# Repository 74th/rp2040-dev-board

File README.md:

# 74th が RP2040/RP2350 を手ではんだ付けしてみたくて作った開発ボード

- [Raspberry PI PICO と同じピン配置で、Flush のサイズを変えたいために、作った開発ボード rp2040 large board](./rp2040-large/)
- [ProMicro ピンアウト開発ボード rp2040 pro micro](./rp2040-promicro/)
- [RP2350の全てのピンを引き足した開発ボード（位置決め治具対応） RP2350A-Full](./rp2350a-full/)
- [RP2040の手はんだ実装支援用位置決め治具 RP2040 Solder Supporter](./rp2040-supporter/)
- [完成後のチェック用に使うファームウェア](rp2040-io-tester/) [rp2040-io-tester.uf2](rp2040-io-tester/rp2040-io-tester.uf2)
- [部品の調達先](./parts/)

## RP2040 手はんだ実装挑戦指南ガイド

74th の実装ノウハウをまとめたガイドを用意しています。初めて挑戦される方はぜひおよみください。

https://docs.google.com/document/d/1oHzV6qEClttqfrnbo-PlUElAemhTQe8-u3ijAKLZYF0/edit#heading=h.1b8zdysibsw9

## 使用しているシンボル、フットプリントライブラリ

https://github.com/74th/my-kicad-parts

## LICENSE

MIT

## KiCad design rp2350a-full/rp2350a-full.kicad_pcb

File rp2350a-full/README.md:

# RP2350A 手はんだ実装挑戦ボード

## v1.0.1

- 回路図 [PDF](./rp2350a-full_v1.0.1_semantics.pdf) [kicanvas](https://kicanvas.org/?github=https%3A%2F%2Fgithub.com%2F74th%2Frp2040-dev-board%2Fblob%2Frp2350-full%2F1.0.1%2Frp2350a-full%2Frp2350a-full.kicad_sch)
- PCB [kicanvas](https://kicanvas.org/?github=https%3A%2F%2Fgithub.com%2F74th%2Frp2040-dev-board%2Fblob%2Frp2350-full%2F1.0.1%2Frp2350a-full%2Frp2350a-full.kicad_pcb)

### Pin Map

### BOM

| Reference    | Name                              | Package         | Quantity |
| ------------ | --------------------------------- | --------------- | -------- |
| C1,C9-17,C19 | Capacitor 0.1uF                   | SMD I0603 M1608 | 11       |
| C2-4,C18     | Capacitor 4.7uF                   | SMD I0603 M1608 | 4        |
| C5-6         | Capacitor 7-33pF                    | SMD I0603 M1608 | 2        |
| C7-8         | Capacitor 10uF                    | SMD I0603 M1608 | 2        |
| D1           | LED Blue                          | SMD I0805 M2012 | 1        |
| J1           | USB Type-C Receptacle             |                 | 1        |
| J2           | Box Pin Header 2x5 Pitch 1.27mm   | TH              | 1        |
| L1           | Inductor 3.3uH                    | SMD I0806 M2016 | 1        |
| R1           | Resistor 200Ω                     | SMD I0603 M1608 | 1        |
| R2           | Resistor 1Ω                       | SMD I0603 M1608 | 1        |
| R3-4         | Resistor 27Ω                      | SMD I0603 M1608 | 2        |
| R5           | Resistor 33Ω                      | SMD I0603 M1608 | 1        |
| R6,R10       | Resistor 1kΩ                      | SMD I0603 M1608 | 2        |
| R7-8         | Resistor 5.1kΩ                    | SMD I0603 M1608 | 2        |
| R9,R11       | Resistor 10kΩ                     | SMD I0603 M1608 | 2        |
| SW1-2        | Button SKRPABE010                 |                 | 2        |
| U1           | MCU Raspberry Pi RP2350A          | QFN56           | 1        |
| U2           | USB Power Protection IC CH213K    | SOT-23          | 1        |
| U3           | Regulator 3.3V SOT-89 AMS1117-3.3 | SOT-90          | 1        |
| U4           | Flash W25Q32JVUU                  | USON-8          | 1        |
| Y1           | Crystal 12MHz                     | SMD 3225        | 1        |

## 実装の手順

実装したときの記録を記事にしています。こちらを実装前に参考にお読みいただけると良いかと思います。

https://74th.hateblo.jp/entry/2025/01/12/222618

かならずフラックスを用意してください。ブリッジした場合にはフラックスを塗って、はんだごてをあてて余分なフラックスを取り除きましょう。

以下の順序で実装することを推奨しています。

1. RP2350A(U1): RP2040 用の[位置決めボード](https://74th.booth.pm/items/5573498)を使えるなら使いましょう。手はんだ実装時のノウハウは
   https://docs.google.com/document/d/1oHzV6qEClttqfrnbo-PlUElAemhTQe8-u3ijAKLZYF0/edit#heading=h.1b8zdysibsw9 にまとめています。
2. USB Type-C: 受動部品実装前の方が、ランドを用いた疎通チェックがやりやすいため。[実装チェックツール](https://74th.booth.pm/items/5812941)を使うと便利です。
3. DCDC 用インダクタ(L1): 付近に囲むように他の部品があるため、先に実装します。
4. W25Q32VSS(U4): 裏面パッドに流すためのランドがあり、その付近に受動部品があり、後から実装が難しいため。
   - 裏面パッドのランドは他の部分より熱が伝わりにくいです。はんだが吸い込まれるまで、十分に加熱してください。
5. AMS1117-3.3(U3): 近くに CH213 があり、実装しにくいため。
6. CH213(U2)
7. 他の抵抗(R1-11)、キャパシタ(C1-19)、水晶発振器(Y1)、LED(D1)
8. スイッチ(SW1-2): サイズが大きく他の部品の実装の邪魔になるため、後から実装する

確認して実装ミスがなさそうであれば、電気的なチェックに進みましょう。

1. VBUS(VB)、5V、3V3、GND(G)間それぞれの抵抗値を計測し、短絡している（0Ω）となっている事がないことを確認する
2. USB を接続し、5V、3V3 と GND 間の電圧を測り、それぞれの電圧が正常であることを確認する
3. L1 と GND 間の電圧を測り、1.1V が出ていることを確認する。
4. PC に USB が認識されるか確認する。

全てのピンが実装できている稼働を確認するファームウェアを作っています。

各ピンが実装漏れている、若しくはブリッジしているのを確認するファームウェアを作っています。

https://github.com/74th/mcu-pin-check-firmware/

以下がファームウェアへのダイレクトリンクです。

https://github.com/74th/mcu-pin-check-firmware/raw/refs/heads/main/release/rp2350.uf2

GNDとジャンパをつなぎ、開発ボードの各スルーホールにジャンパのもう片方でタッチします。すると、USB CDCにてGPIO 8: L、GPIO 8: Hと出力されます。
これにて、全てのピンが接続され、ブリッジされていないことを確認してください。

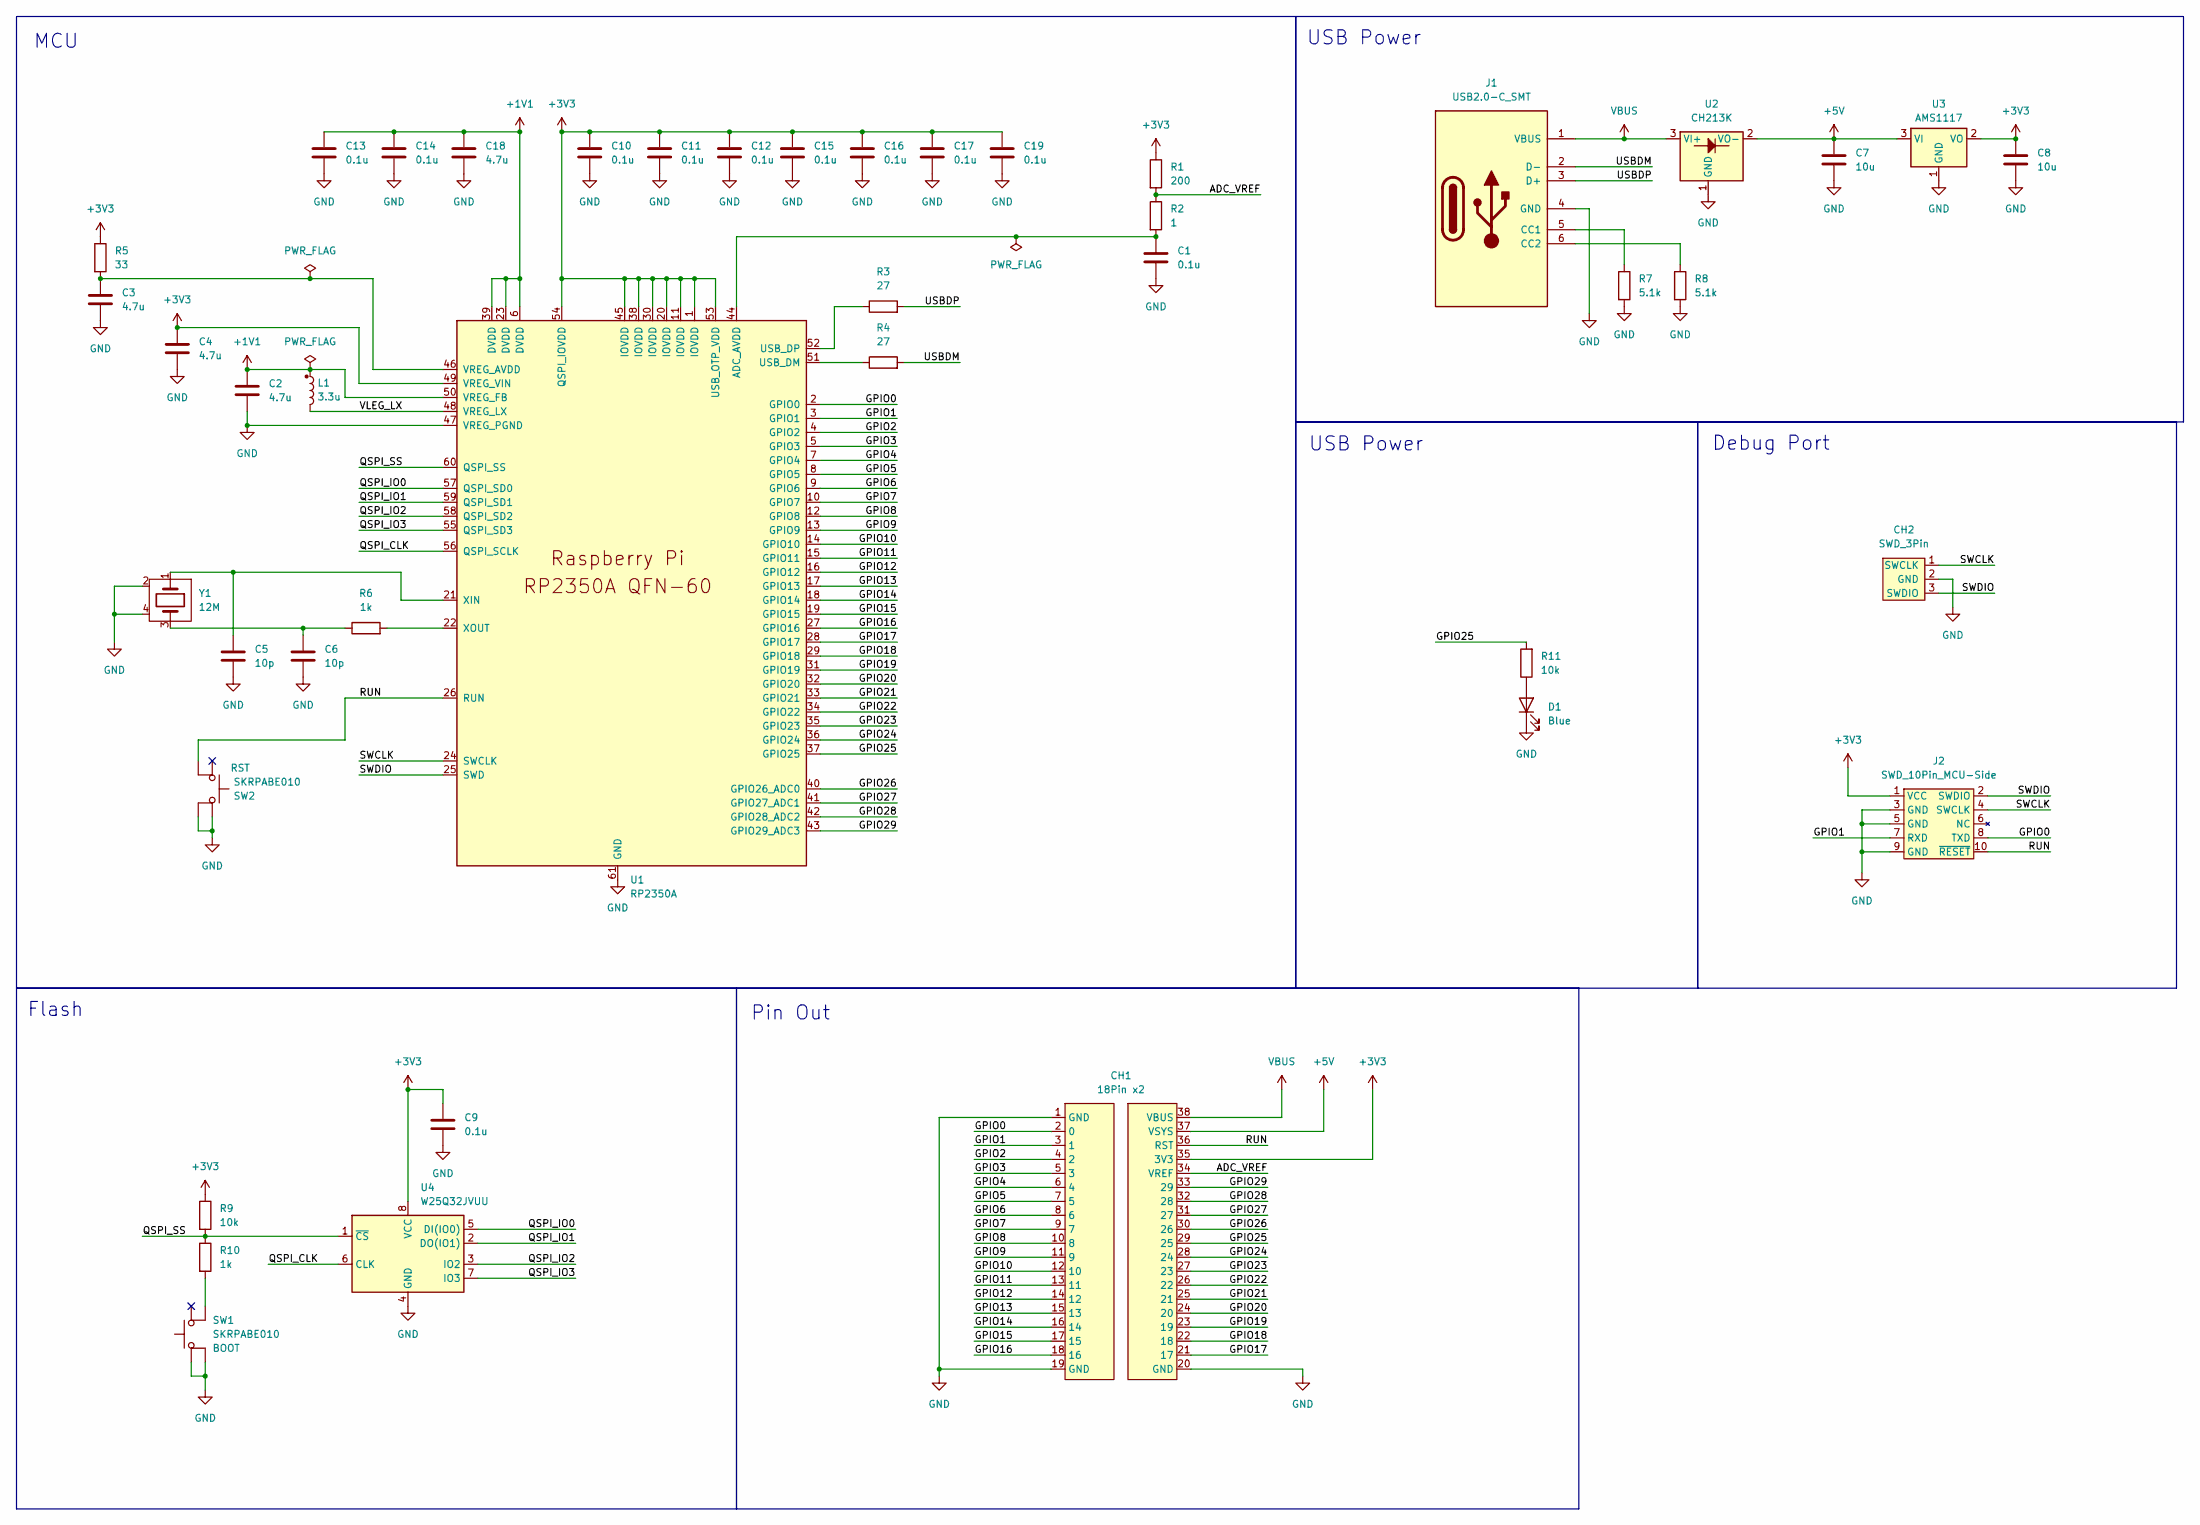
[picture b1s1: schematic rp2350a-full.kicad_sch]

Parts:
C1, C9, C10, C11, C12, C13, C14, C15, C16, C17, C19: 0.1u; Capacitor_0603_1608
C2, C3, C4, C18: 4.7u; Capacitor_0603_1608
C5, C6: 10p; Capacitor_0603_1608
C7, C8: 10u; Capacitor_0603_1608
CH1: 18Pin x2; PinOut_RP2350-Full
CH2: SWD_3Pin; PinOut_Pin_3_2GND
D1: Blue; LED_0805_2012
J1: USB2.0-C_SMT; Connector_USB-C-Receptacle_SMT_12-Pin_Simple
J2: SWD_10Pin_MCU-Side; Connector_HalfPinHeader_SWD
L1: 3.3u; Inductor_0806_2016
R1: 200; Register_0603_1608
R2: 1; Register_0603_1608
R3, R4: 27; Register_0603_1608
R5: 33; Register_0603_1608
R6, R10: 1k; Register_0603_1608
R7, R8: 5.1k; Register_0603_1608
R9, R11: 10k; Register_0603_1608
SW1, SW2: SKRPABE010; Switch_SKRPABE010_Pin-4
U1: RP2350A; Package_QFN-60-1EP_7x7mm_P0.4mm_EP3.4x3.4mm_hand
U2: CH213K; Package_SOT-23
U3: AMS1117; Package_SOT-89-3
U4: W25Q32JVUU; Package_USON-8_3x4mm_P0.8
Y1: 12M; Crystal_SMD_3225-4Pin_3.2x2.5mm_HandSoldering

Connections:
+1V1: C2.1, C13.1, C14.1, C18.1, L1.1, U1.6 (DVDD), U1.23 (DVDD), U1.39 (DVDD), U1.50 (VREG_FB)
+3V3: C4.1, C8.1, C9.1, C10.1, C11.1, C12.1, C15.1, C16.1, C17.1, C19.1, CH1.35 (3V3), J2.1 (VCC), R1.1, R5.1, R9.1, U1.1 (IOVDD), U1.11 (IOVDD), U1.20 (IOVDD), U1.30 (IOVDD), U1.38 (IOVDD), U1.45 (IOVDD), U1.49 (VREG_VIN), U1.53 (USB_OTP_VDD), U1.54 (QSPI_IOVDD), U3.2 (VO), U4.8 (VCC)
+5V: C7.1, CH1.37 (VSYS), U2.2 (VO-), U3.3 (VI)
/ADC_VREF: CH1.34 (VREF), R1.2, R2.1
/GPIO0: CH1.2 (0), J2.8 (TXD), U1.2 (GPIO0)
/GPIO1: CH1.3 (1), J2.7 (RXD), U1.3 (GPIO1)
/GPIO2: CH1.4 (2), U1.4 (GPIO2)
/GPIO3: CH1.5 (3), U1.5 (GPIO3)
/GPIO4: CH1.6 (4), U1.7 (GPIO4)
/GPIO5: CH1.7 (5), U1.8 (GPIO5)
/GPIO6: CH1.8 (6), U1.9 (GPIO6)
/GPIO7: CH1.9 (7), U1.10 (GPIO7)
/GPIO8: CH1.10 (8), U1.12 (GPIO8)
/GPIO9: CH1.11 (9), U1.13 (GPIO9)
/GPIO10: CH1.12 (10), U1.14 (GPIO10)
/GPIO11: CH1.13 (11), U1.15 (GPIO11)
/GPIO12: CH1.14 (12), U1.16 (GPIO12)
/GPIO13: CH1.15 (13), U1.17 (GPIO13)
/GPIO14: CH1.16 (14), U1.18 (GPIO14)
/GPIO15: CH1.17 (15), U1.19 (GPIO15)
/GPIO16: CH1.18 (16), U1.27 (GPIO16)
/GPIO17: CH1.21 (17), U1.28 (GPIO17)
/GPIO18: CH1.22 (18), U1.29 (GPIO18)
/GPIO19: CH1.23 (19), U1.31 (GPIO19)
/GPIO20: CH1.24 (20), U1.32 (GPIO20)
/GPIO21: CH1.25 (21), U1.33 (GPIO21)
/GPIO22: CH1.26 (22), U1.34 (GPIO22)
/GPIO23: CH1.27 (23), U1.35 (GPIO23)
/GPIO24: CH1.28 (24), U1.36 (GPIO24)
/GPIO25: CH1.29 (25), R11.2, U1.37 (GPIO25)
/GPIO26: CH1.30 (26), U1.40 (GPIO26_ADC0)
/GPIO27: CH1.31 (27), U1.41 (GPIO27_ADC1)
/GPIO28: CH1.32 (28), U1.42 (GPIO28_ADC2)
/GPIO29: CH1.33 (29), U1.43 (GPIO29_ADC3)
/QSPI_CLK: U1.56 (QSPI_SCLK), U4.6 (CLK)
/QSPI_IO0: U1.57 (QSPI_SD0), U4.5 (DI(IO0))
/QSPI_IO1: U1.59 (QSPI_SD1), U4.2 (DO(IO1))
/QSPI_IO2: U1.58 (QSPI_SD2), U4.3 (IO2)
/QSPI_IO3: U1.55 (QSPI_SD3), U4.7 (IO3)
/QSPI_SS: R9.2, R10.1, U1.60 (QSPI_SS), U4.1 (~CS)
/RUN: CH1.36 (RST), J2.10 (~RESET), SW2.4, U1.26 (RUN)
/SWCLK: CH2.1 (SWCLK), J2.4 (SWCLK), U1.24 (SWCLK)
/SWDIO: CH2.3 (SWDIO), J2.2 (SWDIO), U1.25 (SWD)
/USBDM: J1.2 (D-), R4.2
/USBDP: J1.3 (D+), R3.2
/VLEG_LX: L1.2, U1.48 (VREG_LX)
GND: C1.2, C2.2, C3.2, C4.2, C5.2, C6.2, C7.2, C8.2, C9.2, C10.2, C11.2, C12.2, C13.2, C14.2, C15.2, C16.2, C17.2, C18.2, C19.2, CH1.1 (GND), CH1.19 (GND), CH1.20 (GND), CH2.2 (GND), D1.1 (K), J1.4 (GND), J2.3 (GND), J2.5 (GND), J2.9 (GND), R7.2, R8.2, SW1.1, SW1.3, SW2.1, SW2.3, U1.47 (VREG_PGND), U1.61 (GND), U2.1 (GND), U3.1 (GND), U4.4 (GND), Y1.2, Y1.4
unnamed: C6.1, R6.1, Y1.3
unnamed: D1.2 (A), R11.1
unnamed: J1.5 (CC1), R7.1
unnamed: J1.6 (CC2), R8.1
unnamed: R10.2, SW1.4
unnamed: C1.1, R2.2, U1.44 (ADC_AVDD)
unnamed: R4.1, U1.51 (USB_DM)
unnamed: R3.1, U1.52 (USB_DP)
unnamed: C3.1, R5.2, U1.46 (VREG_AVDD)
unnamed: C5.1, U1.21 (XIN), Y1.1
unnamed: R6.2, U1.22 (XOUT)
VBUS: CH1.38 (VBUS), J1.1 (VBUS), U2.3 (VI+)

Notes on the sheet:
Flash
Pin Out
USB Power
Debug Port
MCU

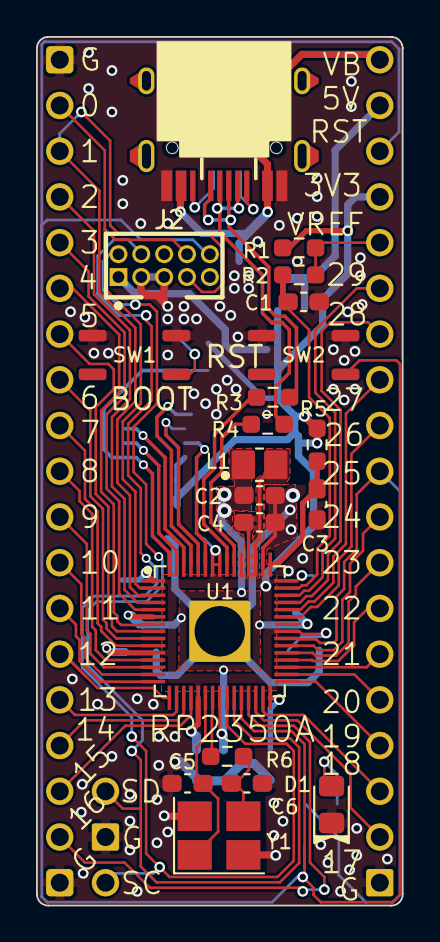
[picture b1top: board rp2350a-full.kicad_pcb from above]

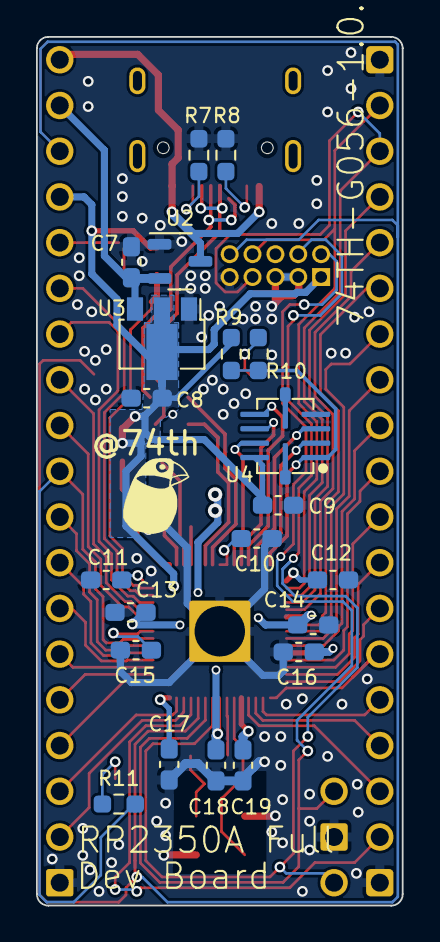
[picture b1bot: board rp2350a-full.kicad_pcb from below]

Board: 2 copper layers, 20.3 x 48.3 mm, 45 parts (23 on the bottom side), 59 nets.

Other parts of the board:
MISC-ACCOUNTTEXT: Logo_74th_text
MISC-ICON: LOGO; Logo_74th_5mm

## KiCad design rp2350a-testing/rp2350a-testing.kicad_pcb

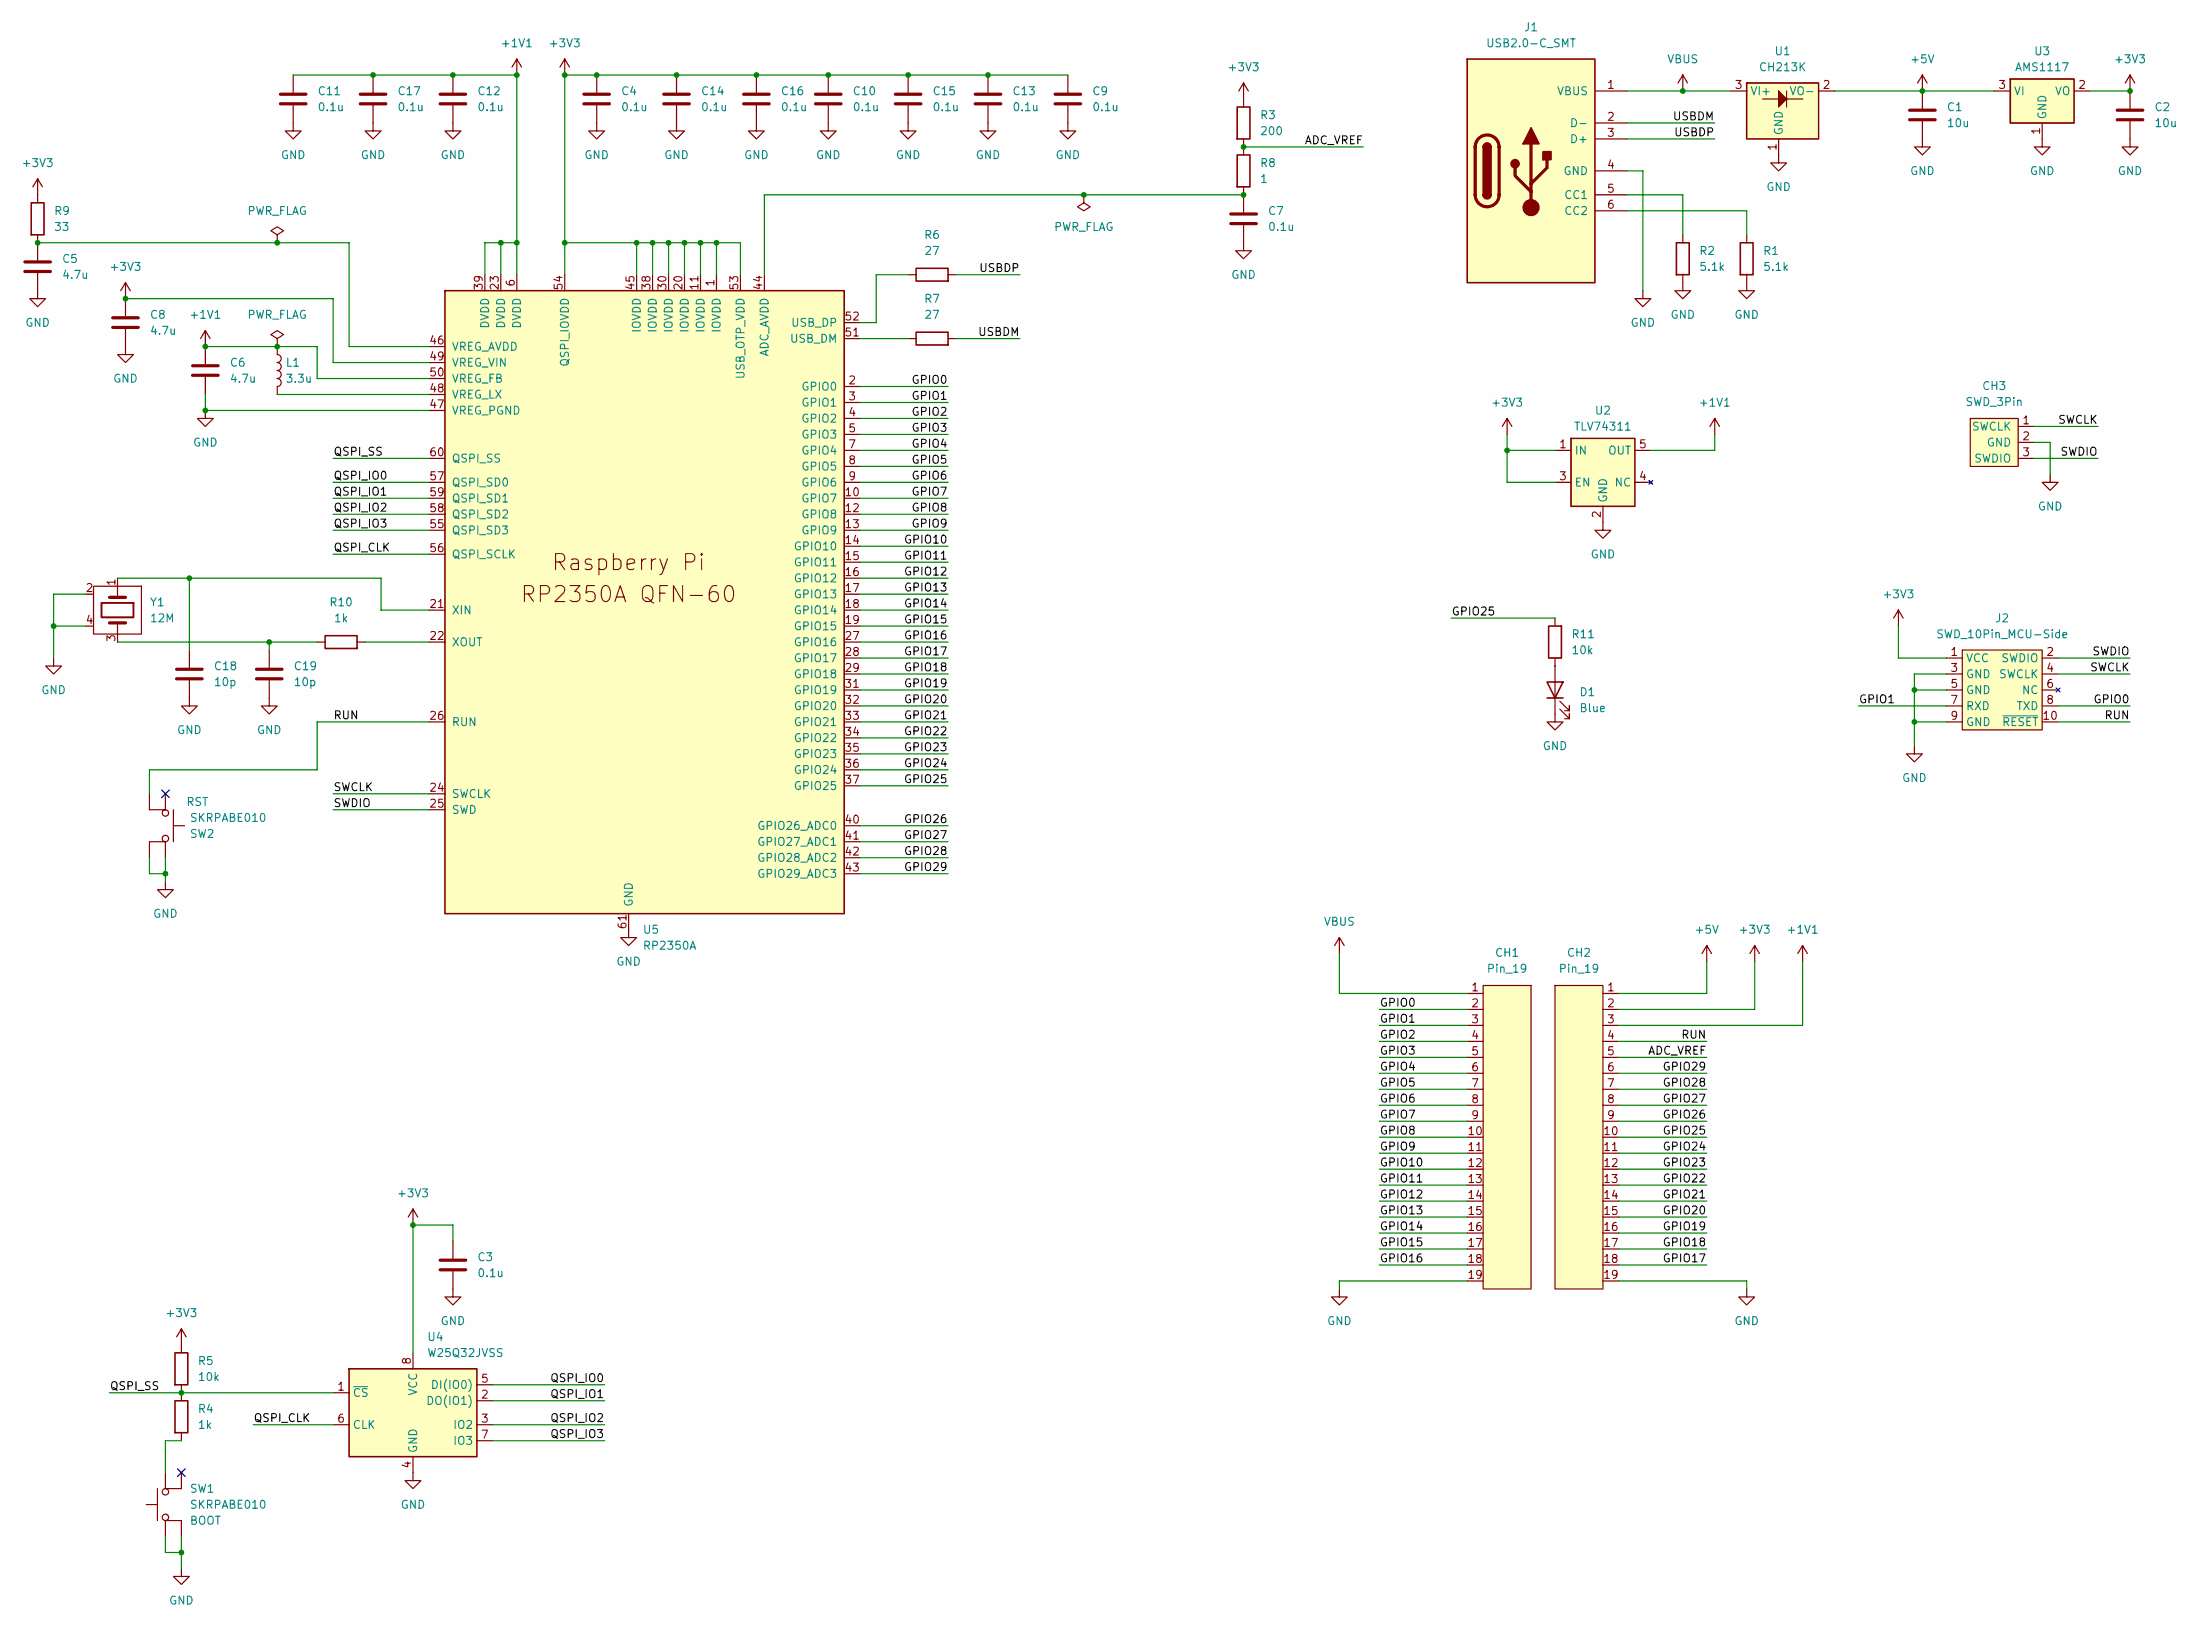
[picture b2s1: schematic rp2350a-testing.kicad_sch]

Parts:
C1, C2: 10u; Capacitor_0603_1608
C3, C4, C9, C10, C11, C12, C13, C14, C15, C16, C17: 0.1u; Capacitor_0402_1005
C5, C6, C8: 4.7u; Capacitor_0402_1005_m
C7: 0.1u; Capacitor_0603_1608
C18, C19: 10p; Capacitor_0402_1005
CH1, CH2: Pin_19; PinOut_Pin_19
CH3: SWD_3Pin; PinOut_Pin_3_2GND
D1: Blue; LED_0805_2012
J1: USB2.0-C_SMT; Connector_USB-C-Receptacle_SMT_12-Pin_Simple
J2: SWD_10Pin_MCU-Side; Connector_HalfPinHeader_SWD
L1: 3.3u; Inductor_4.1x4.5mm_testing
R1, R2: 5.1k; Register_0603_1608
R3: 200; Register_0603_1608
R4: 1k; Register_0603_1608
R5, R11: 10k; Register_0603_1608
R6, R7: 27; Register_0603_1608
R8: 1; Register_0603_1608
R9: 33; Register_0603_1608
R10: 1k; Register_0402_1005
SW1, SW2: SKRPABE010; Switch_SKRPABE010_Pin-4
U1: CH213K; Package_SOT-23
U2: TLV74311; Package_SOT-23-5
U3: AMS1117; Package_SOT-89-3
U4: W25Q32JVSS; Package_USON-8_3x4mm_P0.8
U5: RP2350A; Package_QFN-60-1EP_7x7mm_P0.4mm_EP3.4x3.4mm_hand
Y1: 12M; Crystal_SMD_3225-4Pin_3.2x2.5mm_HandSoldering

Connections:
+1V1: C6.1, C11.1, C12.1, C17.1, CH2.3, L1.1, U2.5 (OUT), U5.6 (DVDD), U5.23 (DVDD), U5.39 (DVDD), U5.50 (VREG_FB)
+3V3: C2.1, C3.1, C4.1, C8.1, C9.1, C10.1, C13.1, C14.1, C15.1, C16.1, CH2.2, J2.1 (VCC), R3.1, R5.1, R9.1, U2.1 (IN), U2.3 (EN), U3.2 (VO), U4.8 (VCC), U5.1 (IOVDD), U5.11 (IOVDD), U5.20 (IOVDD), U5.30 (IOVDD), U5.38 (IOVDD), U5.45 (IOVDD), U5.49 (VREG_VIN), U5.53 (USB_OTP_VDD), U5.54 (QSPI_IOVDD)
+5V: C1.1, CH2.1, U1.2 (VO-), U3.3 (VI)
/ADC_VREF: CH2.5, R3.2, R8.1
/GPIO0: CH1.2, J2.8 (TXD), U5.2 (GPIO0)
/GPIO1: CH1.3, J2.7 (RXD), U5.3 (GPIO1)
/GPIO2: CH1.4, U5.4 (GPIO2)
/GPIO3: CH1.5, U5.5 (GPIO3)
/GPIO4: CH1.6, U5.7 (GPIO4)
/GPIO5: CH1.7, U5.8 (GPIO5)
/GPIO6: CH1.8, U5.9 (GPIO6)
/GPIO7: CH1.9, U5.10 (GPIO7)
/GPIO8: CH1.10, U5.12 (GPIO8)
/GPIO9: CH1.11, U5.13 (GPIO9)
/GPIO10: CH1.12, U5.14 (GPIO10)
/GPIO11: CH1.13, U5.15 (GPIO11)
/GPIO12: CH1.14, U5.16 (GPIO12)
/GPIO13: CH1.15, U5.17 (GPIO13)
/GPIO14: CH1.16, U5.18 (GPIO14)
/GPIO15: CH1.17, U5.19 (GPIO15)
/GPIO16: CH1.18, U5.27 (GPIO16)
/GPIO17: CH2.18, U5.28 (GPIO17)
/GPIO18: CH2.17, U5.29 (GPIO18)
/GPIO19: CH2.16, U5.31 (GPIO19)
/GPIO20: CH2.15, U5.32 (GPIO20)
/GPIO21: CH2.14, U5.33 (GPIO21)
/GPIO22: CH2.13, U5.34 (GPIO22)
/GPIO23: CH2.12, U5.35 (GPIO23)
/GPIO24: CH2.11, U5.36 (GPIO24)
/GPIO25: CH2.10, R11.2, U5.37 (GPIO25)
/GPIO26: CH2.9, U5.40 (GPIO26_ADC0)
/GPIO27: CH2.8, U5.41 (GPIO27_ADC1)
/GPIO28: CH2.7, U5.42 (GPIO28_ADC2)
/GPIO29: CH2.6, U5.43 (GPIO29_ADC3)
/QSPI_CLK: U4.6 (CLK), U5.56 (QSPI_SCLK)
/QSPI_IO0: U4.5 (DI(IO0)), U5.57 (QSPI_SD0)
/QSPI_IO1: U4.2 (DO(IO1)), U5.59 (QSPI_SD1)
/QSPI_IO2: U4.3 (IO2), U5.58 (QSPI_SD2)
/QSPI_IO3: U4.7 (IO3), U5.55 (QSPI_SD3)
/QSPI_SS: R4.1, R5.2, U4.1 (~CS), U5.60 (QSPI_SS)
/RUN: CH2.4, J2.10 (~RESET), SW2.4, U5.26 (RUN)
/SWCLK: CH3.1 (SWCLK), J2.4 (SWCLK), U5.24 (SWCLK)
/SWDIO: CH3.3 (SWDIO), J2.2 (SWDIO), U5.25 (SWD)
/USBDM: J1.2 (D-), R7.2
/USBDP: J1.3 (D+), R6.2
GND: C1.2, C2.2, C3.2, C4.2, C5.2, C6.2, C7.2, C8.2, C9.2, C10.2, C11.2, C12.2, C13.2, C14.2, C15.2, C16.2, C17.2, C18.2, C19.2, CH1.19, CH2.19, CH3.2 (GND), D1.1 (K), J1.4 (GND), J2.3 (GND), J2.5 (GND), J2.9 (GND), R1.2, R2.2, SW1.1, SW1.3, SW2.1, SW2.3, U1.1 (GND), U2.2 (GND), U3.1 (GND), U4.4 (GND), U5.47 (VREG_PGND), U5.61 (GND), Y1.2, Y1.4
unnamed: C19.1, R10.1, Y1.3
unnamed: D1.2 (A), R11.1
unnamed: J1.5 (CC1), R2.1
unnamed: J1.6 (CC2), R1.1
unnamed: R4.2, SW1.2
unnamed: C7.1, R8.2, U5.44 (ADC_AVDD)
unnamed: R7.1, U5.51 (USB_DM)
unnamed: R6.1, U5.52 (USB_DP)
unnamed: C5.1, R9.2, U5.46 (VREG_AVDD)
unnamed: L1.2, U5.48 (VREG_LX)
unnamed: C18.1, U5.21 (XIN), Y1.1
unnamed: R10.2, U5.22 (XOUT)
VBUS: CH1.1, J1.1 (VBUS), U1.3 (VI+)

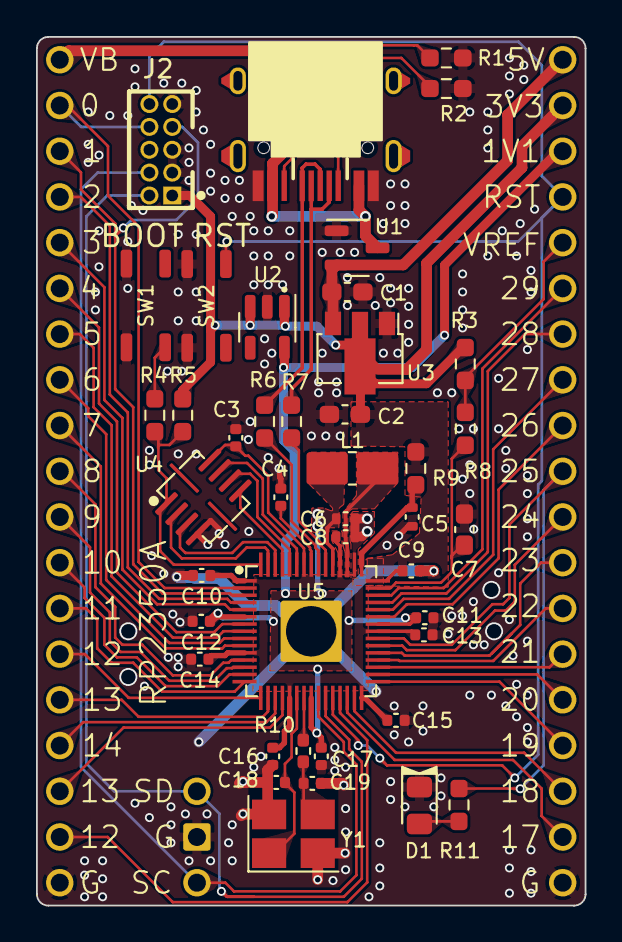
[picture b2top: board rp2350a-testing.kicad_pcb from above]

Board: 2 copper layers, 30.5 x 48.3 mm, 46 parts (1 on the bottom side), 59 nets.

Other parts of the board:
MISC-ICON: LOGO; Logo_74th_7.5mm

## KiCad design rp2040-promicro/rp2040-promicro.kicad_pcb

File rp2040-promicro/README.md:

# RP2040 Pro Micro ピンアウト開発ボード \[74th-012\]

発注用ガーバーファイルは [release page](https://github.com/74th/rp2040-dev-board/releases) を確認ください。

- Booth キット販売ページ [https://74th.booth.pm/items/4492441](https://74th.booth.pm/items/4492441)

## 2.0.1-2

2.0.2 は KiCad 8.0 で出力し直したもので、2.0.1 と差異はありません。

- 回路図: [PDF](rp2040-promicro-v2.0.1-semantics.pdf) [kicanvas](https://kicanvas.org/?github=https%3A%2F%2Fgithub.com%2F74th%2Frp2040-dev-board%2Fblob%2Frp2040-promicro%2F2.0.1%2Frp2040-promicro%2Frp2040-promicro.kicad_sch)
- PCB 2.0.1 [kicanvas](https://kicanvas.org/?github=https%3A%2F%2Fgithub.com%2F74th%2Frp2040-dev-board%2Fblob%2Frp2040-promicro%2F2.0.1%2Frp2040-promicro%2Frp2040-promicro.kicad_pcb)
- PCB 2.0.2 [kicanvas](https://kicanvas.org/?github=https%3A%2F%2Fgithub.com%2F74th%2Frp2040-dev-board%2Fblob%2Frp2040-promicro%2F2.0.2%2Frp2040-promicro%2Frp2040-promicro.kicad_pcb)

| Reference      | Name                              | Quantity |
| -------------- | --------------------------------- | -------- |
| C1, C4, C7-C12 | Capacitor 0805 100nF              | 8        |
| C2, C3         | Capacitor 0805 10uF               | 2        |
| C5, C6         | Capacitor 0805 1uF                | 2        |
| C13, C14       | Capacitor 0805 10-27pF            | 2        |
| F1             | PolyFuse 1812 KT6-1100SMDI        | 1        |
| J1             | USB Type-C Receptacle             | 1        |
| R1, R4, R5     | Resistor 0805 1kΩ                 | 3        |
| R2, R3         | Resistor 0805 5.1kΩ               | 2        |
| R6             | Resistor 0805 10kΩ                | 1        |
| R7, R8         | Resistor 0805 10-27Ω              | 2        |
| SW1            | Button SKRPABE010                 | 1        |
| U1             | Regulator 3.3V SOT-89 AMS1117-3.3 | 1        |
| U2             | Flash SOIC-8 W25Q128JVS           | 1        |
| U3             | MCU Raspberry Pi RP2040           | 1        |
| Y1             | Crystal 3225 12MHz                | 1        |

※ 大変申し訳ありません。2023/09/17 まで誤った部品表が 2.0.1 として掲載されておりました。

## 2.0.0

- 回路図: [PDF](rp2040-promicro-v2.0.0-semantics.pdf) [kicanvas](https://kicanvas.org/?github=https%3A%2F%2Fgithub.com%2F74th%2Frp2040-dev-board%2Fblob%2Frp2040-promicro%2F2.0.1%2Frp2040-promicro%2Frp2040-promicro.kicad_sch)
- PCB [PDF](rp2040-promicro-v2.0.0-pcb.pdf) [kicanvas](https://kicanvas.org/?github=https%3A%2F%2Fgithub.com%2F74th%2Frp2040-dev-board%2Fblob%2Frp2040-promicro%2F2.0.1%2Frp2040-promicro%2Frp2040-promicro.kicad_pcb)

| Designator                      | Parts                             | Quantity |
| ------------------------------- | --------------------------------- | -------- |
| R1, R2                          | 0805 レジスタ 27.4R               | 2        |
| R3, R7, R8                      | 0805 レジスタ 1kR                 | 3        |
| R4, R5                          | 0805 レジスタ 5.1kR               | 2        |
| R6                              | 0805 レジスタ 10kR                | 1        |
| C1, C2, C6, C7, C8, C9,C10, C13 | 0805 キャパシタ 100nF             | 8        |
| C11, C12                        | 0805 キャパシタ 27pF              | 2        |
| C14, C15                        | 0805 キャパシタ 10uF              | 2        |
| C3, C5                          | 0805 キャパシタ 1uF               | 2        |
| F1                              | リセッタブルフィーズ KT6-1100SMDI | 1        |
| J1                              | USB Type-C ソケット               | 1        |
| J2                              | ピンヘッダー(ProMicro Left)       | 1        |
| J3                              | ピンヘッダー(ProMicro Left)       | 1        |
| SW1                             | SKRPABE010                        | 1        |
| U1                              | MCU RP2040                        | 1        |
| U2                              | FLASH W25Q32JVS                   | 1        |
| U3                              | レギュレータ AMS1117(SOT-89)      | 1        |
| Y1                              | クリスタル 12MHz 3225             | 1        |

## v1.1.0

- 回路図 [rp2040-promicro-v1.1.0-semantics.pdf](rp2040-promicro-v1.1.0-semantics.pdf)
- PCB [rp2040-promicro-v1.1.0-pcb.pdf](rp2040-promicro-v1.1.0-pcb.pdf)

### 部品表

| Item | Qty | Reference(s)                         | Value             | LibPart                            | Footprint                                             | Datasheet                                                                        |
| ---- | --- | ------------------------------------ | ----------------- | ---------------------------------- | ----------------------------------------------------- | -------------------------------------------------------------------------------- |
| 1    | 9   | C1, C2, C4, C6, C7, C8, C9, C10, C13 | 100nF             | Device:C                           | rp2040-dev-board:Capacitor_0805_2012                  | ~                                                                                |
| 2    | 2   | C3, C5                               | 1uF               | Device:C                           | rp2040-dev-board:Capacitor_0805_2012                  | ~                                                                                |
| 3    | 2   | C11, C12                             | 27pF              | Device:C                           | rp2040-dev-board:Capacitor_0603_1608                  | ~                                                                                |
| 4    | 2   | C14, C15                             | 10uF              | Device:C                           | rp2040-dev-board:Capacitor_0805_2012                  | ~                                                                                |
| 5    | 1   | J2                                   | ProMicro-LeftPin  | rp2040-dev-board:ProMicro-LeftPin  | rp2040-dev-board:LeftPin                              |                                                                                  |
| 6    | 1   | J3                                   | ProMicro-RightPin | rp2040-dev-board:ProMicro-RightPin | rp2040-dev-board:RightPin                             |                                                                                  |
| 7    | 1   | P1                                   | USB2.0_C_12pin    | rp2040-dev-board:USB2.0_C_12pin    | rp2040-dev-board:USB-C-12-Pin-MidMount-ali-v2         | https://www.usb.org/sites/default/files/documents/usb_type-c.zip                 |
| 8    | 2   | R1, R2                               | 27.4R             | Device:R                           | rp2040-dev-board:Resistor_0805_2012                   | ~                                                                                |
| 9    | 2   | R3, R7                               | 1kR               | Device:R                           | rp2040-dev-board:Resistor_0805_2012                   | ~                                                                                |
| 10   | 2   | R4, R5                               | 5.1kR             | Device:R                           | rp2040-dev-board:Resistor_0805_2012                   | ~                                                                                |
| 11   | 1   | R6                                   | 10kR              | Device:R                           | rp2040-dev-board:Resistor_0805_2012                   | ~                                                                                |
| 12   | 1   | SW1                                  | SW_Push           | Switch:SW_Push                     | rp2040-dev-board:BOOT                                 | ~                                                                                |
| 13   | 1   | U1                                   | RP2040            | rp2040-dev-board:RP2040            | rp2040-dev-board:RP2040_hand                          |                                                                                  |
| 14   | 1   | U2                                   | W25Q128JVS        | Memory_Flash:W25Q128JVS            | rp2040-dev-board:W25Q16-128JV-SOIC                    | http://www.winbond.com/resource-files/w25q128jv_dtr%20revc%2003272018%20plus.pdf |
| 15   | 1   | U3                                   | AZ1117-3.3        | Regulator_Linear:AZ1117-3.3        | rp2040-dev-board:Regulator-AMS1117-SOT-223            | https://www.diodes.com/assets/Datasheets/AZ1117.pdf                              |
| 16   | 1   | Y1                                   | Crystal_GND24     | Device:Crystal_GND24               | Crystal:Crystal_SMD_3225-4Pin_3.2x2.5mm_HandSoldering | ~                                                                                |

## RP2040 手はんだ実装挑戦指南ガイド

74th の実装ノウハウをまとめたガイドを用意しています。初めて挑戦される方はぜひおよみください。

https://docs.google.com/document/d/1oHzV6qEClttqfrnbo-PlUElAemhTQe8-u3ijAKLZYF0/edit#heading=h.1b8zdysibsw9

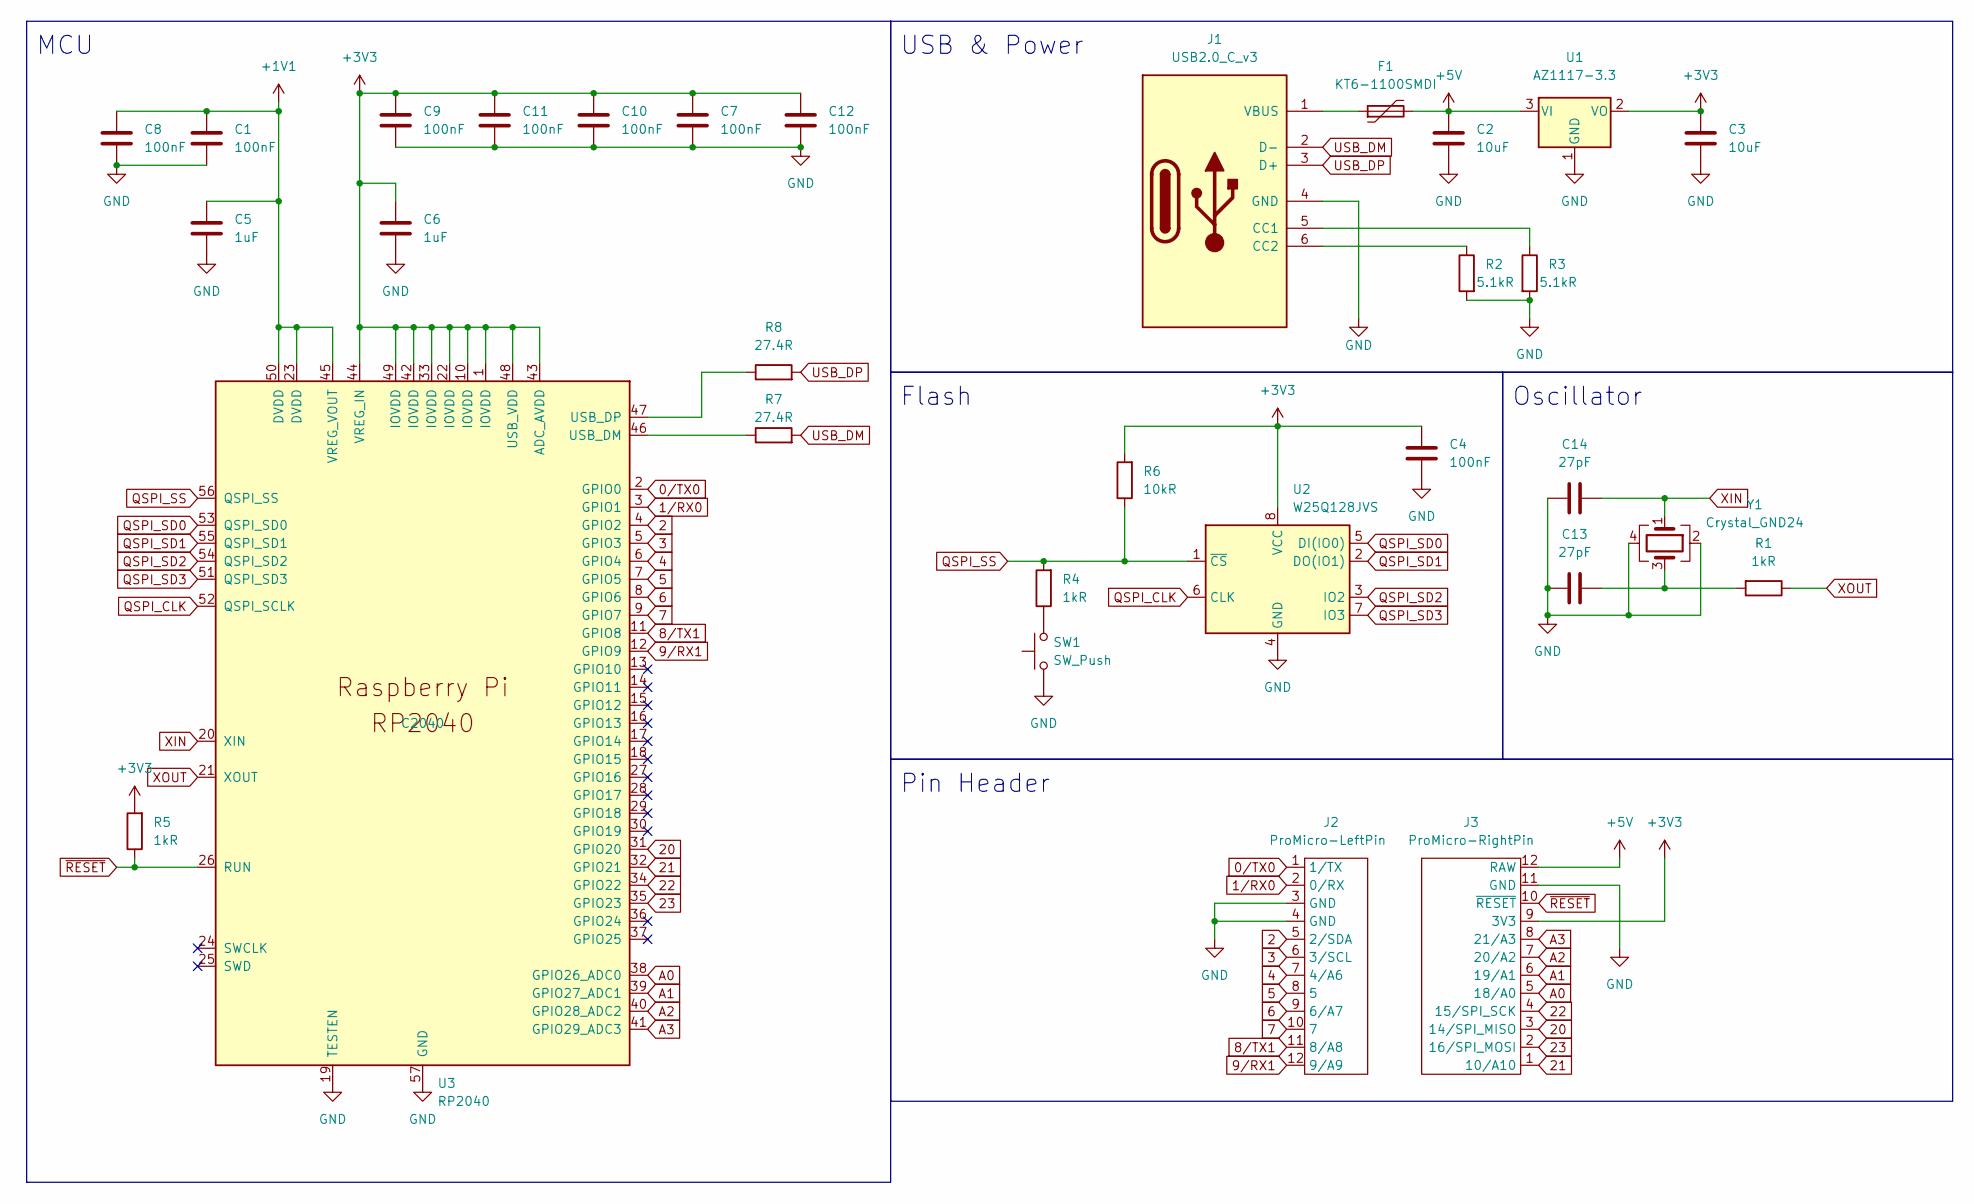
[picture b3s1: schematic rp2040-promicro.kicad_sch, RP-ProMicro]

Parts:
C1, C4, C7, C8, C9, C10, C11, C12: 100nF; Capacitor_0805_2012
C2, C3: 10uF; Capacitor_0805_2012
C5, C6: 1uF; Capacitor_0805_2012
C13, C14: 27pF; Capacitor_0805_2012
F1: KT6-1100SMDI; ResettableFuse_KT6-1100SMDI
J1: USB2.0_C_v3; USB-C-12-Pin-SMD
J2: ProMicro-LeftPin; ProMicro_LIKE_LEFT
J3: ProMicro-RightPin; ProMicro_LIKE_RIGHT
R1, R4, R5: 1kR; Register_0805_2012
R2, R3: 5.1kR; Register_0805_2012
R6: 10kR; Register_0805_2012
R7, R8: 27.4R; Register_0805_2012
SW1: SW_Push; SKRPABE010
U1: AZ1117-3.3; Regulator_AMS1117_SOT-89
U2: W25Q128JVS; W25Q16-128JV-SOIC
U3: RP2040; RP2040_hand; MPN C2040
Y1: Crystal_GND24; Crystal_SMD_3225-4Pin_3.2x2.5mm_HandSoldering

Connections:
0/TX0: J2.1 (1/TX), U3.2 (GPIO0)
1/RX0: J2.2 (0/RX), U3.3 (GPIO1)
2: J2.5 (2/SDA), U3.4 (GPIO2)
3: J2.6 (3/SCL), U3.5 (GPIO3)
4: J2.7 (4/A6), U3.6 (GPIO4)
5: J2.8 (5), U3.7 (GPIO5)
6: J2.9 (6/A7), U3.8 (GPIO6)
7: J2.10 (7), U3.9 (GPIO7)
8/TX1: J2.11 (8/A8), U3.11 (GPIO8)
9/RX1: J2.12 (9/A9), U3.12 (GPIO9)
20: J3.3 (14/SPI_MISO), U3.31 (GPIO20)
21: J3.1 (10/A10), U3.32 (GPIO21)
22: J3.4 (15/SPI_SCK), U3.34 (GPIO22)
23: J3.2 (16/SPI_MOSI), U3.35 (GPIO23)
+1V1: C1.1, C5.1, C8.1, U3.23 (DVDD), U3.45 (VREG_VOUT), U3.50 (DVDD)
+3V3: C3.1, C4.1, C6.1, C7.1, C9.1, C10.1, C11.1, C12.1, J3.9 (3V3), R5.2, R6.2, U1.2 (VO), U2.8 (VCC), U3.1 (IOVDD), U3.10 (IOVDD), U3.22 (IOVDD), U3.33 (IOVDD), U3.42 (IOVDD), U3.43 (ADC_AVDD), U3.44 (VREG_IN), U3.48 (USB_VDD), U3.49 (IOVDD)
+5V: C2.1, F1.2, J3.12 (RAW), U1.3 (VI)
A0: J3.5 (18/A0), U3.38 (GPIO26_ADC0)
A1: J3.6 (19/A1), U3.39 (GPIO27_ADC1)
A2: J3.7 (20/A2), U3.40 (GPIO28_ADC2)
A3: J3.8 (21/A3), U3.41 (GPIO29_ADC3)
GND: C1.2, C2.2, C3.2, C4.2, C5.2, C6.2, C7.2, C8.2, C9.2, C10.2, C11.2, C12.2, C13.1, C14.1, J1.4 (GND), J2.3 (GND), J2.4 (GND), J3.11 (GND), R2.2, R3.2, SW1.1, U1.1 (GND), U2.4 (GND), U3.19 (TESTEN), U3.57 (GND), Y1.2, Y1.4
unnamed: C13.2, R1.2, Y1.3
unnamed: F1.1, J1.1 (VBUS)
unnamed: J1.5 (CC1), R3.1
unnamed: J1.6 (CC2), R2.1
unnamed: R8.1, U3.47 (USB_DP)
unnamed: R7.1, U3.46 (USB_DM)
unnamed: R4.1, SW1.2
QSPI_CLK: U2.6 (CLK), U3.52 (QSPI_SCLK)
QSPI_SD0: U2.5 (DI(IO0)), U3.53 (QSPI_SD0)
QSPI_SD1: U2.2 (DO(IO1)), U3.55 (QSPI_SD1)
QSPI_SD2: U2.3 (IO2), U3.54 (QSPI_SD2)
QSPI_SD3: U2.7 (IO3), U3.51 (QSPI_SD3)
QSPI_SS: R4.2, R6.1, U2.1 (~CS), U3.56 (QSPI_SS)
USB_DM: J1.2 (D-), R7.2
USB_DP: J1.3 (D+), R8.2
XIN: C14.2, U3.20 (XIN), Y1.1
XOUT: R1.1, U3.21 (XOUT)
~RESET: J3.10 (~RESET), R5.1, U3.26 (RUN)

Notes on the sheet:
Pin Header
Flash
MCU
Oscillator
USB & Power

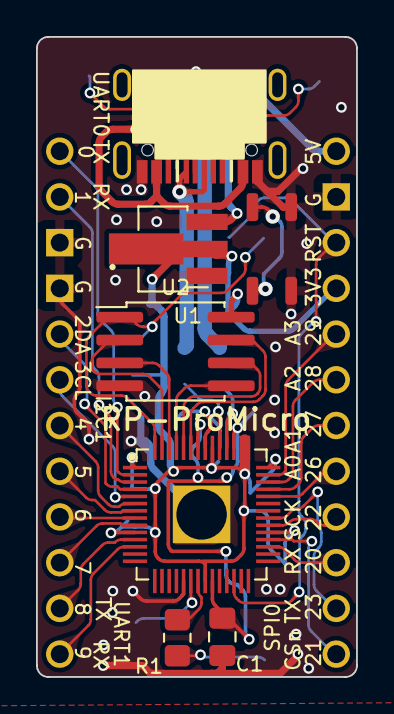
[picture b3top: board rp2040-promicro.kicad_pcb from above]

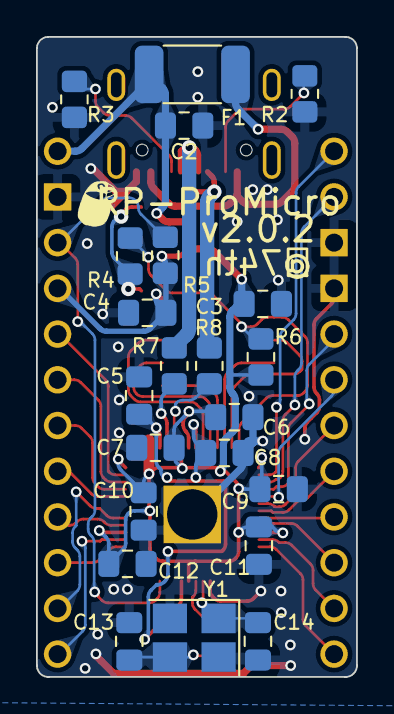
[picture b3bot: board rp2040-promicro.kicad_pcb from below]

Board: 2 copper layers, 17.8 x 35.6 mm, 31 parts (22 on the bottom side), 40 nets.
